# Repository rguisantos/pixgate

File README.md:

# PixGate

**Controlador de acesso por pagamento Pix** — placa controladora que libera uma trava elétrica quando um pagamento Pix é confirmado, com aceitação opcional de cédulas (noteiro) e moedas (moedeiro) através de entradas optoisoladas.

Projeto de hardware **open** desenvolvido de forma programática: toda a placa (netlist, colocação, footprints custom) é descrita em Python e gerada como arquivo `.kicad_pcb` nativo do **KiCad 9**, validado com o DRC oficial via `kicad-cli`.

> **Status: v1.0 em desenvolvimento.** Netlist auditada (polaridade de todos os diodos + LED verificada) e colocação concluída — courtyards zerados no DRC. Roteamento e pass de silk em andamento — ver [Estado do desenvolvimento](#estado-do-desenvolvimento) e o [WORKLOG](WORKLOG.md).

---

## Como funciona

1. O **ESP32-C5-WROOM-1-N4** (Wi-Fi 6 dual-band + BLE 5) conecta-se à internet e consulta o status de um pagamento Pix (API/PSP — parte de firmware).
2. Pagamento confirmado → o firmware aciona o transistor **AO3400A**, que energiza a bobina do relé **Songle SRD-12VDC-SL-C** (contato NO 10 A).
3. O contato do relé fecha o circuito da **trava elétrica 12 V** ligada ao bornier **KF301**, com snubber RC e TVS na saída.
4. Entradas de dinheiro físico chegam isoladas por **3× PC817**: noteiro, moedeiro e botão externo (12 V, conectores JST-XH).
5. O **display TFT 1.54"** (frontal, via soquete 1×8) mostra status/valor; **USB-C** serve para programação e serial; **LED** de status na frente.

## Especificações da placa

| Parâmetro | Valor |
| --- | --- |
| Dimensões | 55 × 75 mm |
| Camadas | 2 (F.Cu / B.Cu), 1,6 mm |
| Alimentação | 12 V DC via jack DC-005 |
| Buck 12 V → 5 V | TPS54331DDA (SOIC-8 EP), 3 A, L 6,8 µH |
| LDO 5 V → 3,3 V | TLV1117LV33DCYR (SOT-223) |
| MCU | ESP32-C5-WROOM-1-N4 (antena na borda superior) |
| Saída a relé | SRD-12VDC-SL-C, contato NO 10 A @ 12 V |
| Entradas isoladas | 3× PC817 (noteiro / moedeiro / botão) |
| USB | USB-C (USBLC6-2SC6 + PTC 1206L + diodo SS14) |
| Conectores | DC-005, KF301-2P 5,08 mm, 3× JST-XH, USB-C HRO TYPE-C-31-M-12 |
| Frontal | TFT 1.54" (soquete 1×8 P2,54), LED 0805 + R 1 k |
| Botões | RST, BOOT, CFG (PTS645) |
| Pads de teste | TX0, RX0, GND |
| Furos de montagem | 4× M3 |

Layout proposital: **frente** só com display e LED (vista limpa); **verso** com toda a eletrônica e potência.

## Regras de compra e montagem (fixadas na conferência contra datasheet)

- **Display:** só o módulo TFT 1.54" **ST7789 SPI de 8 pinos**, ordem **GND VCC SCL SDA RST DC CS BL** — módulo de 7 pinos (sem CS) **não serve**.
- **Relé:** antes de encomendar, conferir a pinagem do relé comprado contra o datasheet do **fabricante** dele (a conferência usou a lib oficial KiCad pós-#1003 + um footprint comunitário; o PDF da Songle estava bloqueado no ambiente).
- **PC817:** dot do pino 1 no canto superior esquerdo de cada opto (pad 1 quadrado + entalhe de silk).
- **JTAG por USB: desligado** nesta revisão — o R10 puxa o GPIO7 (pino 9 do módulo) para +3V3, exigido pelo §4.4 do datasheet; a **gravação pela USB-C não é afetada**; para habilitar JTAG-USB, mover o R10 para GND.

Checklist completo de compra, montagem e primeira energização em [docs/conferencia-datasheet.md](docs/conferencia-datasheet.md).

## Blocos funcionais

| Bloco | Componentes | Função |
| --- | --- | --- |
| MCU + RF | U1 ESP32-C5-WROOM-1-N4, C18/C19, R7, C20 | Cérebro Wi-Fi 6; EN com RC de reset |
| Buck 12→5 V | U2 TPS54331DDA, L1 6,8 µH, D5 SS54, C1–C9, R20/R21/R22, R26 | Regulação de 5 V, compensação e soft-start dimensionados |
| LDO 3,3 V | U3 TLV1117LV33DCYR, C10–C13 | Rails de 3,3 V digital |
| Driver do relé | Q1 AO3400A, R3 100R, R4 10k, D3 SS14 (flyback), K1 | Bobina 12 V chaveada por GPIO |
| Saída protegida | R23 100R + C24 100nF (snubber), D6 SMBJ16A (TVS), D7 SS54 | Proteção do contato NO da trava |
| Entradas isoladas | OPT1–3 PC817, R13–R15 10k, R16–R18 2,2k | 12 V → 3,3 V com isolamento galvânico |
| USB-C | J6, U4 USBLC6-2SC6, R1/R2 5,1k (CC), F2 PTC, D2 SS14, C16/C17 | VBUS or-ing com buck, ESD, enumeração |
| Display | J7 soquete 1×8, R5/R6 33R (série SPI), R10–R12 10k | TFT frontal com terminação série |
| Proteção de entrada | F1 PTC, D1 SS54, D4 SMBJ18A (TVS), C1–C3 | 12 V reverso/sobretensão/transitórios |

## Estrutura do repositório

```
pixgate/
├── hardware/            # Gerador programático da placa
│   ├── gen_board.py     # Netlist completa + colocação de todos os componentes
│   ├── pcb_lib.py       # Parser/serializador S-expression + utilitários KiCad 9
│   │                    #   (flip back-side, embed com nets, builders de footprint)
│   ├── net_audit.py     # Auditoria da netlist (polaridade, pinagem, nets órfãs)
│   ├── check_pads.py    # Dump de pads/nets finais (conferência vs datasheet)
│   └── board_header.txt # Cabeçalho .kicad_pcb validado (layers/setup padrão)
├── validation/          # Evidências de validação com o DRC do KiCad 9
│   ├── test_board.py    # Teste 1: módulo no verso, nets, segmento
│   ├── test_board2.py   # Teste 2: header + módulo flipado + Edge.Cuts
│   ├── boards/          # Boards de teste gerados (.kicad_pcb)
│   └── drc/             # Relatórios DRC (bisection de erros, flip, rotação)
├── tools/               # Utilitários do fluxo de pesquisa/desenvolvimento
│   ├── redirect.c       # Shim LD_PRELOAD: /usr/share/kicad -> KiCad extraído
│   ├── extract_svg_text.py  # Extração de texto/coords de SVG de land pattern
│   └── parse_wiki_usb.py    # Pinout USB-C extraído da Wikipédia
└── docs/
    ├── references.md    # Datasheets, libs e designs de referência usados
    └── conferencia-datasheet.md  # Rodada 4: conferência pin-a-pin vs datasheet
```

## Gerando a placa

Requisitos:

- Python 3.8+
- KiCad 9 (`kicad-cli` no PATH) — usado para validar o arquivo gerado
- Biblioteca oficial de footprints [KiCad/kicad-footprints](https://github.com/KiCad/kicad-footprints) **em formato 9.x** (a versão de 2020 @7ebfa6b usa formato legado `module`/`fp_arc` que o KiCad 9 não carrega; o pacote Debian `kicad-footprints` 9.0.2 funciona)
- Footprints Espressif [espressif/kicad-libraries](https://github.com/espressif/kicad-libraries)

Os caminhos das bibliotecas estão no topo de `hardware/gen_board.py`:

```python
FPDIR = os.path.expanduser('~/kicad-root/root/usr/share/kicad/footprints')  # kicad 9.0.2 extraído sem root
ESPDIR = os.path.expanduser('~/kicad-libs/kicad-libraries/footprints/Espressif.pretty')
```

Ajuste `FPDIR`/`ESPDIR` para o seu layout (ex.: `/usr/share/kicad/footprints` numa instalação normal de Linux) e rode:

```bash
python3 hardware/serialize.py           # gera hardware/pixgate.kicad_pcb (board completo)
python3 hardware/net_audit.py           # auditoria da netlist (exit 1 se achar problema)
python3 hardware/place_check.py         # conflitos de colocação (cobre/courtyard) instantâneos
```

## Validação (DRC)

O arquivo `.kicad_pcb` gerado é validado com o DRC oficial:

```bash
kicad-cli pcb drc --severity-all --output report.rpt hardware/pixgate.kicad_pcb
```

A pasta `validation/drc/` guarda a trilha de evidências do desenvolvimento: um board mínimo com DRC 100% limpo (`test3`), a bisection que isolou a causa de erros de outline (`bisect_*`), o caso com outline fechado e nets controladas (`ok`) e o teste de rotação de footprint a 90° (`rot_test`). Detalhes no [WORKLOG](WORKLOG.md).

## Estado do desenvolvimento

- [x] Arquitetura da placa e seleção de componentes (BOM virtual completa)
- [x] Biblioteca Python de manipulação de `.kicad_pcb` (`pcb_lib.py`), com semântica de flip para o verso validada
- [x] Footprints custom: soquete do display, relé SRD, KF301, SOIC-8 com EP, pads de teste, furos M3
- [x] Netlist completa (51 redes nomeadas) e **auditada** — polaridade de D1–D7 + LED1 e pinagem de J1/U4/Q1 verificadas (`hardware/net_audit.py`)
- [x] Formato de arquivo validado no DRC do KiCad 9 (`kicad-cli`), incluindo a convenção de rotação de pads do formato 9
- [x] Serialização do board completo (`hardware/pixgate.kicad_pcb` carrega no pcbnew)
- [x] Colocação concluída (lotes 1–6: shorts, clearances e courtyards zerados no DRC; no place_check só resta o artefato de bbox do BarrelJack)
- [x] Conferência contra datasheet (rodada 4): U1/K1/OPT1-3/J7 verificados pin-a-pin — **board inalterado** ([docs/conferencia-datasheet.md](docs/conferencia-datasheet.md))
- [x] Pass de silk pré-Gerbers — **silk DRC limpo** (0 warnings)
- [x] H4 movido para y=97.5 (edge clearance 0,9 mm ≥ 0,5 mm)
- [x] `route.py`: zonas GND (F.Cu/B.Cu), 4 vias térmicas U2 pad 9, stitching bordas (com filtro anti-colisão)
- [ ] Roteamento — **manual** no pcbnew (decisão de ROI — ver [WORKLOG.md](WORKLOG.md) entrada 16)
- [ ] `route.py`: **não gera trilhas**; não rodar de novo após roteamento manual
- [ ] DRC final limpo + exportação de Gerbers (ver [docs/pre-fab-checklist.md](docs/pre-fab-checklist.md))
- [ ] Firmware (fora do escopo deste repositório por enquanto)

## Créditos e fontes

- Footprints: [KiCad/kicad-footprints](https://github.com/KiCad/kicad-footprints) e [espressif/kicad-libraries](https://github.com/espressif/kicad-libraries)
- Símbolos (verificação do jack DC-005): pacote Debian `kicad-symbols` 9.0.2-1 (upstream [KiCad/kicad-symbols](https://github.com/KiCad/kicad-symbols)) — ver [docs/references.md](docs/references.md)
- Designs de referência: [SparkFun Thing Plus ESP32-C6](https://github.com/sparkfun/SparkFun_Thing_Plus_ESP32_C6) e [SparkFun Thing Plus ESP32-S3](https://github.com/sparkfun/SparkFun_Thing_Plus_ESP32-S3)
- Datasheets e pinouts: ver [docs/references.md](docs/references.md)

---

⚠️ **Aviso:** projeto em desenvolvimento, ainda não fabricado nem testado fisicamente. Revise o design antes de qualquer uso em produção.

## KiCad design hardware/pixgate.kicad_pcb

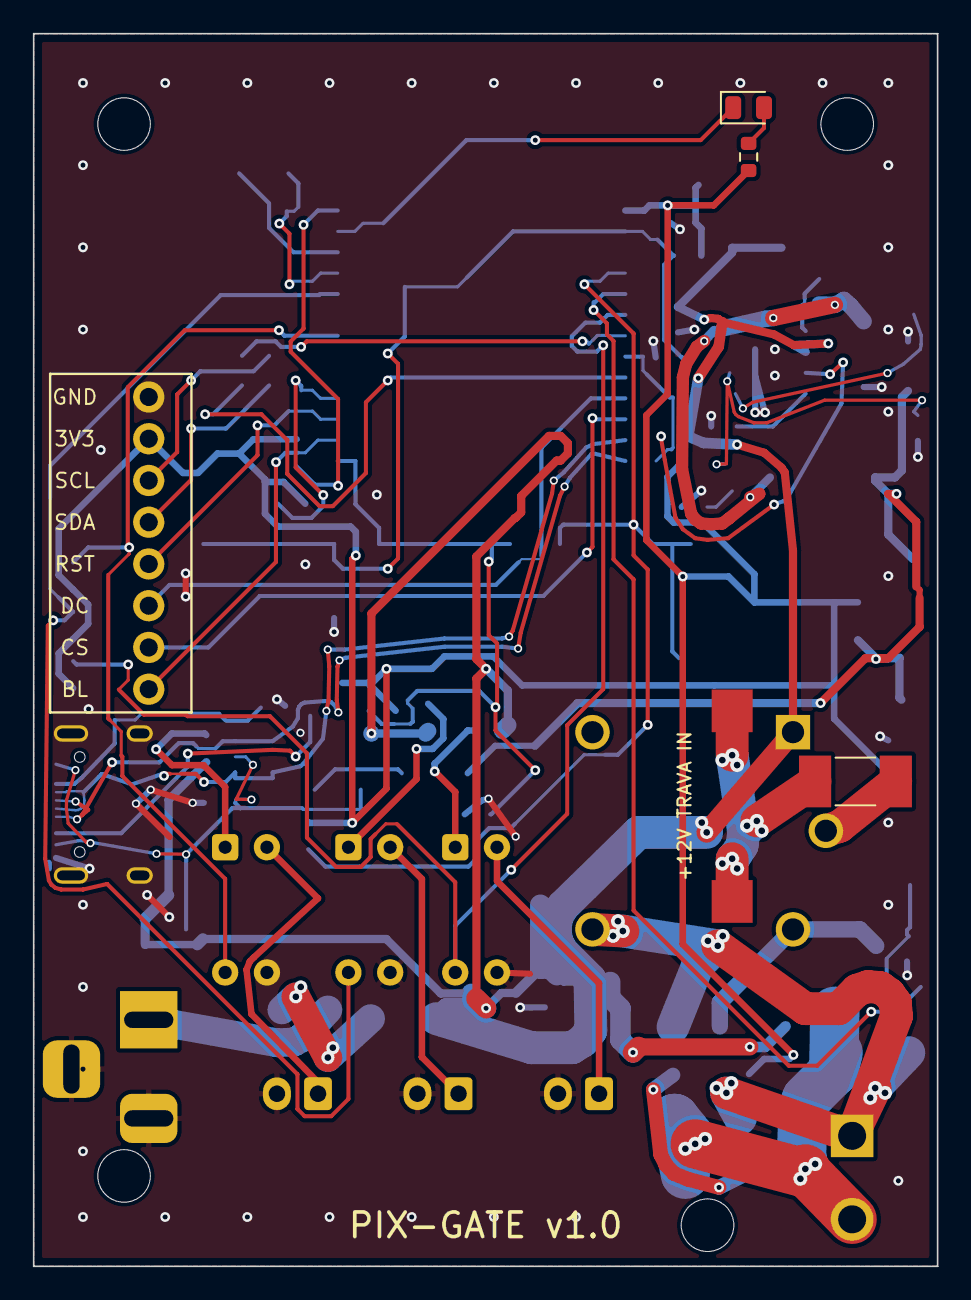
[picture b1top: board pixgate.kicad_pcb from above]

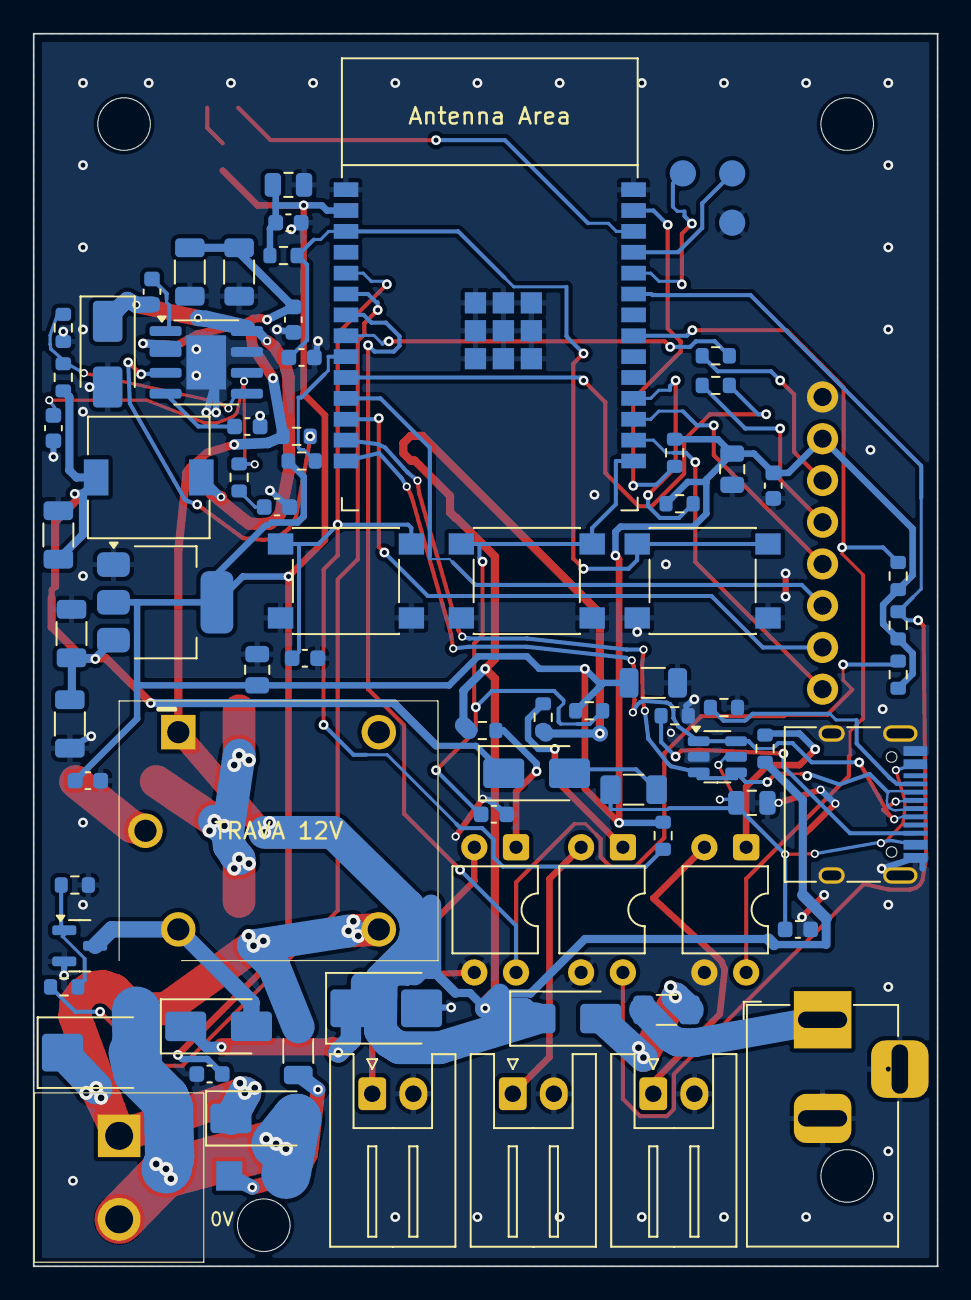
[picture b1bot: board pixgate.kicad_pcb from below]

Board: 2 copper layers, 55.0 x 75.0 mm, 87 parts (82 on the bottom side), 54 nets.

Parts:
C1, C2: 10uF/25V; C_1206_3216Metric
C3, C4, C9, C13, C15, C17, C19, C20, C21, C22: 100nF; C_0603_1608Metric
C5, C6: 33uF/10V; C_1206_3216Metric
C7: 4.7nF; C_0603_1608Metric
C8: 39pF; C_0603_1608Metric
C10, C12: 22uF; C_1206_3216Metric
C11, C14, C16, C18: 10uF; C_0805_2012Metric
C23: 1uF; C_0603_1608Metric
C24: 100nF; C_1206_3216Metric_NoSilk
D1, D5, D7: SS54; D_SMA
D2, D3: SS14; D_SMA
D4: SMBJ18A; D_SMB
D6: SMBJ16A; D_SMB
F1: 1206L110/16; Fuse_1206_3216Metric
F2: 1206L050/24; Fuse_1206_3216Metric
F3: 0454007.MR; Fuse_Littelfuse-NANO2-451_453
H1, H2, H3, H4: M3; MountingHole_3.2mm_M3
J1: DC-005 12V; BarrelJack_Horizontal
J2: KF301 TRAVA; TerminalBlock_KF301-2P-5.08mm
J3: JST-XH NOTEIRO; JST_XH_S2B-XH-A_1x02_P2.50mm_Horizontal
J4: JST-XH MOEDEIRO; JST_XH_S2B-XH-A_1x02_P2.50mm_Horizontal
J5: JST-XH BOTAO; JST_XH_S2B-XH-A_1x02_P2.50mm_Horizontal
J6: USB-C; USB_C_Receptacle_HRO_TYPE-C-31-M-12
J7: TFT 1.54; DisplaySocket_1x08_P2.54mm
J8: 2060-451/998-404; TerminalBlock_WAGO_2060-451_1P
K1: SRD-12VDC-SL-C; Relay_SPDT_Songle_SRD
L1: 6.8uH; L_7.3x7.3_H3.5
LED1: STATUS; LED_0805_2012Metric
OPT1, OPT2, OPT3: PC817; DIP-4_W7.62mm
Q1: AO3400A; SOT-23
R1, R2: 5.1k; R_0603_1608Metric
R3: 100R; R_0603_1608Metric
R4, R7, R8, R9, R10, R11, R12, R13, R14, R15, R20: 10k; R_0603_1608Metric
R5, R6: 33R; R_0603_1608Metric
R16, R17, R18: 2.2k; R_0603_1608Metric
R19: 1k; R_0603_1608Metric
R21: 1.91k; R_0603_1608Metric
R22: 49.9k; R_0603_1608Metric
R23: 100R; R_1206_3216Metric
R26: 100k; R_0603_1608Metric
SW1: RST; SW_SPST_PTS645
SW2: BOOT; SW_SPST_PTS645
SW3: CFG; SW_SPST_PTS645
TP1: TX0; TestPad_TX0
TP2: RX0; TestPad_RX0
TP3: GND; TestPad_GND
U1: ESP32-C5-WROOM-1-N4; ESP32-C5-WROOM-1
U2: TPS54331DDA; SOIC-8-1EP_3.9x4.9mm_P1.27mm_EP2.41x3.3mm
U3: TLV1117LV33DCYR; SOT-223-3_TabPin2
U4: USBLC6-2SC6; SOT-23-6

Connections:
+3V3: C11.2, C12.2, C13.1, C14.1, C15.1, C18.1, C19.1, C23.1, J7.2, R7.1, R8.1, R9.1, R10.1, R11.1, R12.1, R13.2, R14.2, R15.2, R19.1, U1.2, U3.2
+5V: C5.2, C6.2, C10.1, D2.1, L1.2, R20.2, U3.3
+12V: C1.1, C2.1, C3.1, D1.1, D3.1, D4.1, K1.A1, R16.2, R17.2, R18.2, R26.1, U2.2
+12V_IN: F1.1, J1.1
+12V_LOCK: F3.2, K1.COM
+12V_LOCK_IN: F3.1, J8.1
BOOT_C: C4.1, U2.1
BTN1: C21.1, R8.2, SW2.1, U1.15
BTN2: C22.1, R9.2, SW3.1, U1.5
BTN_A: OPT3.1, R18.1
BTN_SIG: J5.1, OPT3.2
CC1: J6.A5, R1.1
CC2: J6.B5, R2.1
COIN_A: OPT2.1, R17.1
COIN_SIG: J4.1, OPT2.2
COMP_X: C8.1, R22.1, U2.6
COMP_Y: C7.1, R22.2
DISP_BL: J7.8, U1.16
DISP_CS: J7.7, U1.12
DISP_DC: J7.6, U1.11
DISP_RST: J7.5, U1.17
EN: C20.1, R7.2, SW1.1, U1.3
EN_BK: R26.2, U2.3
F12V: D1.2, F1.2
FB: R20.1, R21.1, U2.5
GND: C1.2, C2.2, C3.2, C5.1, C6.1, C7.2, C8.2, C9.2, C10.2, C11.1, C12.1, C13.2, C14.2, C15.2, C16.2, C17.2, C18.2, C19.2, C20.2, C21.2, C22.2, C23.2, D4.2, D5.2, J1.2, J1.3, J3.2, J4.2, J5.2, J6.A1, J6.A12, J6.B1, J6.B12, J6.S1, J7.1, OPT1.3, OPT2.3, OPT3.3, Q1.2, R1.2, R2.2, R4.2, R21.2, SW1.2, SW2.2, SW3.2, TP3.1, U1.1, U1.28, U1.29, U2.7, U2.9, U3.1, U4.2
GND_LOCK: C24.2, D6.2, D7.2, J2.2
IN_BTN: OPT3.4, R15.1, U1.7
IN_COIN: OPT2.4, R14.1, U1.23
IN_NOTE: OPT1.4, R13.1, U1.21
IO7_PU: R10.2, U1.9
IO26_PU: R11.2, U1.27
IO27_PU: R12.2, U1.18
LED_A: LED1.2, R19.2
LED_K: LED1.1, U1.26
MOSI_D: J7.4, R6.1
MOSI_M: R6.2, U1.10
NOTE_A: OPT1.1, R16.1
NOTE_SIG: J3.1, OPT1.2
RELAY_COIL: D3.2, K1.A2, Q1.3
RLY_DRV: R3.1, U1.6
RLY_GATE: Q1.1, R3.2, R4.1
RX0: TP2.1, U1.24
SCK_D: J7.3, R5.1
SCK_M: R5.2, U1.8
SS_C: C9.1, U2.4
SW: C4.2, D5.1, L1.1, U2.8
TRAVA_NO: D6.1, D7.1, J2.1, K1.NO, R23.1
TRAVA_NO2: C24.1, R23.2
TX0: TP1.1, U1.25
USB_5V_F: D2.2, F2.2
USB_DN: J6.A7, J6.B7, U1.13, U4.3, U4.4
USB_DP: J6.A6, J6.B6, U1.14, U4.1, U4.6
USB_VBUS: C16.1, C17.1, F2.1, J6.A4, J6.A9, J6.B4, J6.B9, U4.5

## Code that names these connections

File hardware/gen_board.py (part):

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U1_NETS = {1:'GND', 2:'+3V3', 3:'EN', 5:'BTN2', 6:'RLY_DRV', 7:'IN_BTN',
           8:'SCK_M', 9:'IO7_PU', 10:'MOSI_M', 11:'DISP_DC', 12:'DISP_CS', 13:'USB_DN', 14:'USB_DP',
           15:'BTN1', 16:'DISP_BL', 17:'DISP_RST', 18:'IO27_PU', 21:'IN_NOTE', 23:'IN_COIN',
           24:'RX0', 25:'TX0', 26:'LED_K', 27:'IO26_PU', 28:'GND', 29:'GND'}  # pino 9 = GPIO7 (strapping/JTAG, FSPID nao usado): destino do pull-up R10
for padn, nname in U1_NETS.items():
    u1.pin(padn, nname)

# --- U2: TPS54331DDA buck (back) ---
u2 = P('U2', 'TPS54331DDA', ('Package_SO', 'SOIC-8-1EP_3.9x4.9mm_P1.27mm_EP2.41x3.3mm'), 69.5, 45, 0)
u2.ref_pos(0, -6)  # move ref down from default
u2.pin(1, 'BOOT_C').pin(2, '+12V').pin(3, 'EN_BK').pin(4, 'SS_C')
u2.pin(5, 'FB').pin(6, 'COMP_X').pin(7, 'GND').pin(8, 'SW').pin(9, 'GND')

# --- U3: TLV1117LV33DCYR (back) ---
u3 = P('U3', 'TLV1117LV33DCYR', ('Package_TO_SOT_SMD', 'SOT-223-3_TabPin2'), 72, 59.6, 0)
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# --- U4: USBLC6-2SC6 (back) ---
u4 = P('U4', 'USBLC6-2SC6', ('Package_TO_SOT_SMD', 'SOT-23-6'), 38.4, 69.0, 0)  # lote 6: x-1.0 (39.4->38.4) — sai do courtyard do F2 (+0.77), F2 fica | y-1.0: TVS colado em J6/F2/C16
u4.ref_pos(0, -3)
u4.pin(1, 'USB_DP').pin(2, 'GND').pin(3, 'USB_DN').pin(4, 'USB_DN').pin(5, 'USB_VBUS').pin(6, 'USB_DP')

# --- Q1: AO3400A relay driver (back) ---
q1 = P('Q1', 'AO3400A', ('Package_TO_SOT_SMD', 'SOT-23'), 77.2, 80.5, 0)  # x+0.2: folga do courtyard do K1 (0.37mm)
q1.pin(1, 'RLY_GATE').pin(2, 'GND').pin(3, 'RELAY_COIL')

# --- Optocouplers (back) ---
opt1 = P('OPT1', 'PC817', ('Package_DIP', 'DIP-4_W7.62mm'), 36.65, 74.5, 90)  # fileira -1.35 (colisao de corpo com K1; pinos 4 alinhados)
opt1.pin(1, 'NOTE_A').pin(2, 'NOTE_SIG').pin(3, 'GND').pin(4, 'IN_NOTE')
opt2 = P('OPT2', 'PC817', ('Package_DIP', 'DIP-4_W7.62mm'), 44.15, 74.5, 90)
opt2.pin(1, 'COIN_A').pin(2, 'COIN_SIG').pin(3, 'GND').pin(4, 'IN_COIN')
opt3 = P('OPT3', 'PC817', ('Package_DIP', 'DIP-4_W7.62mm'), 50.65, 74.5, 90)
opt3.pin(1, 'BTN_A').pin(2, 'BTN_SIG').pin(3, 'GND').pin(4, 'IN_BTN')  # fix netlist: pino 2 era GND — BTN_SIG ficou orfa e o LED sempre aceso

# --- K1: relay SRD-12VDC-SL-C (back) ---
k1 = P('K1', 'SRD-12VDC-SL-C', fp_relay_srd(), 65.1, 73.5, 0)  # x+0.6 + fileira -1.35: resolve colisao FISICA OPT3/K1 (0.86mm) com folga ~0.6mm dos 2 lados
k1.pin('A1', '+12V').pin('A2', 'RELAY_COIL').pin('COM', '+12V_LOCK').pin('NC', '').pin('NO', 'TRAVA_NO')

# --- Diodes (back) ---
d1 = P('D1', 'SS54', ('Diode_SMD', 'D_SMA'), 47.5, 84.93, 0).pin(1, '+12V').pin(2, 'F12V')  # lote 4: encaixe na faixa livre real [83.17..86.69] (3.52mm); y=84.95 invadiria J3/J4 em 0.01 — fix netlist: pino 1 = catodo (D_SMA), serie J1->F1->D1->rail: K no rail
d2 = P('D2', 'SS14', ('Diode_SMD', 'D_SMA'), 49.4, 70, 0).pin(1, '+5V').pin(2, 'USB_5V_F')  # lote 6: x+0.4 (49->49.4) — sai do courtyard do F2 (+0.12) | fix netlist: or-ing USB->+5V estava invertido (pad 1 = catodo)
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d4 = P('D4', 'SMBJ18A', ('Diode_SMD', 'D_SMB'), 58.55, 84.3, 0).pin(1, '+12V').pin(2, 'GND')  # lote 4: courtyard 4.5mm nao cabe na faixa; frente do J5 (gap 0.14) e abaixo do K1 (gap 0.55); no caminho natural do +12V rumo a D3/J5
d5 = P('D5', 'SS54', ('Diode_SMD', 'D_SMA'), 75.5, 44.5, 90).pin(1, 'SW').pin(2, 'GND')
d6 = P('D6', 'SMBJ16A', ('Diode_SMD', 'D_SMB'), 76.1, 87, 0).pin(1, 'TRAVA_NO').pin(2, 'GND_LOCK')
d7 = P('D7', 'SS54', ('Diode_SMD', 'D_SMA'), 66, 91, 0).pin(1, 'TRAVA_NO').pin(2, 'GND_LOCK')
d7.ref_pos(0, -4)

# --- Fuses (back) ---
f1 = P('F1', '1206L110/16', ('Fuse', 'Fuse_1206_3216Metric'), 41.5, 84.4, 0).pin(1, '+12V_IN').pin(2, 'F12V')  # lote 4: y+0.4 libera OPT1/OPT2 (gap 0.10)
f2 = P('F2', '1206L050/24', ('Fuse', 'Fuse_1206_3216Metric'), 43.5, 71, 0).pin(1, 'USB_VBUS').pin(2, 'USB_5V_F')
f3 = P('F3', '0454007.MR', ('Fuse', 'Fuse_Littelfuse-NANO2-451_453'),
       75, 70.5, 0, side='F').pin(1, '+12V_LOCK_IN').pin(2, '+12V_LOCK')

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
# --- Buttons (back, mid board) ---
sw1 = P('SW1', 'RST', ('Button_Switch_SMD', 'SW_SPST_PTS645'), 39.3, 58.3, 0).pin(1, 'EN').pin(2, 'GND')  # lote 6: y+0.3 — sai do courtyard do U1 (corredor dos botoes)
sw2 = P('SW2', 'BOOT', ('Button_Switch_SMD', 'SW_SPST_PTS645'), 50, 58.3, 0).pin(1, 'BTN1').pin(2, 'GND')  # lote 6: y+0.3 — sai do courtyard do U1
sw3 = P('SW3', 'CFG', ('Button_Switch_SMD', 'SW_SPST_PTS645'), 61, 58.3, 0).pin(1, 'BTN2').pin(2, 'GND')  # lote 6: y+0.3 — sai do courtyard do U1
sw3.ref_pos(0, 4)

# --- Connectors (back) ---
j1 = P('J1', 'DC-005 12V', ('Connector_BarrelJack', 'BarrelJack_Horizontal'), 32, 85, 270)
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j2 = P('J2', 'KF301 TRAVA', fp_kf301(), 74.8, 94.6, 90).pin(1, 'TRAVA_NO').pin(2, 'GND_LOCK')
j2.ref_pos(0, -6)
j8 = P('J8', '2060-451/998-404', fp_wago_2060_451(), 67.5, 72, side='F')
j8.pin(1, '+12V_LOCK_IN')
j3 = P('J3', 'JST-XH NOTEIRO', ('Connector_JST', 'JST_XH_S2B-XH-A_1x02_P2.50mm_Horizontal'), 42.3, 89.5, 0)  # lote 6: x-1.2 — fileira JST desloca p/ esquerda (J3<->J4, J1<->J3)
j3.pin(1, 'NOTE_SIG').pin(2, 'GND')
j4 = P('J4', 'JST-XH MOEDEIRO', ('Connector_JST', 'JST_XH_S2B-XH-A_1x02_P2.50mm_Horizontal'), 50.85, 89.5, 0)  # lote 6: x-0.65 — J4<->J5/J3
j4.ref_pos(0, -4)
j4.pin(1, 'COIN_SIG').pin(2, 'GND')
j5 = P('J5', 'JST-XH BOTAO', ('Connector_JST', 'JST_XH_S2B-XH-A_1x02_P2.50mm_Horizontal'), 59.4, 89.5, 0)  # lote 6: x-0.6 — J5<->D7 (D7 fica preso entre J5 e J2)
j5.ref_pos(0, -4)
j5.pin(1, 'BTN_SIG').pin(2, 'GND')  # fix netlist: pino 2 era +12V — botao seco fecha BTN_SIG->GND (padrao J3/J4: sinal no 1, GND no 2)
j6 = P('J6', 'USB-C', ('Connector_USB', 'USB_C_Receptacle_HRO_TYPE-C-31-M-12'), 30.4, 71.9, 90)
for pn in ('A1','B1','A12','B12'): j6.pin(pn, 'GND')
for pn in ('A4','A9','B4','B9'): j6.pin(pn, 'USB_VBUS')
j6.pin('A5', 'CC1').pin('B5', 'CC2')
j6.pin('A6', 'USB_DP').pin('B6', 'USB_DP').pin('A7', 'USB_DN').pin('B7', 'USB_DN')
j6.pin('A8', '').pin('B8', '').pin('S1', 'GND')

# --- J7: display socket (FRONT) ---
j7 = P('J7', 'TFT 1.54', fp_display_socket(), 32, 56, 0, side='F')
j7.ref_pos(0, 12)
j7.pin(1, 'GND').pin(2, '+3V3').pin(3, 'SCK_D').pin(4, 'MOSI_D')
j7.pin(5, 'DISP_RST').pin(6, 'DISP_DC').pin(7, 'DISP_CS').pin(8, 'DISP_BL')

# --- LED (front) ---
led1 = P('LED1', 'STATUS', ('LED_SMD', 'LED_0805_2012Metric'), 68.5, 29.5, 0, side='F')
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r19 = P('R19', '1k', ('Resistor_SMD', 'R_0603_1608Metric'), 68.5, 32.5, 90, side='F')
r19.ref_pos(0, -3)
r19.pin(1, '+3V3').pin(2, 'LED_A')  # netfix3 (fechamento item 2): antes LED_K->GND — LED sempre aceso com GPIO25 so sentindo o no; agora serie no anodo limita a corrente em qualquer estado do pino (a nota "nunca dirigir a LOW" do WORKLOG deixa de existir)

# --- Test pads (back) ---
tp1 = P('TP1', 'TX0', fp_testpad('TX0'), 37.5, 33.5, 0).pin(1, 'TX0')
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

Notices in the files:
hardware/pixgate.kicad_pcb:
PIX-GATE v1.0  rguisantos 2026  CC-BY-SA
